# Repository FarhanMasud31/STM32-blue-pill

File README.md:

learning kicad

STM32 blue pill

followed theses as reference:

https://github.com/Jzuni97/STM32-Blue-Pill/tree/main

https://www.youtube.com/watch?v=aVUqaB0IMh4&t=274s

schematic

front copper layer

back copper layer

3D layout

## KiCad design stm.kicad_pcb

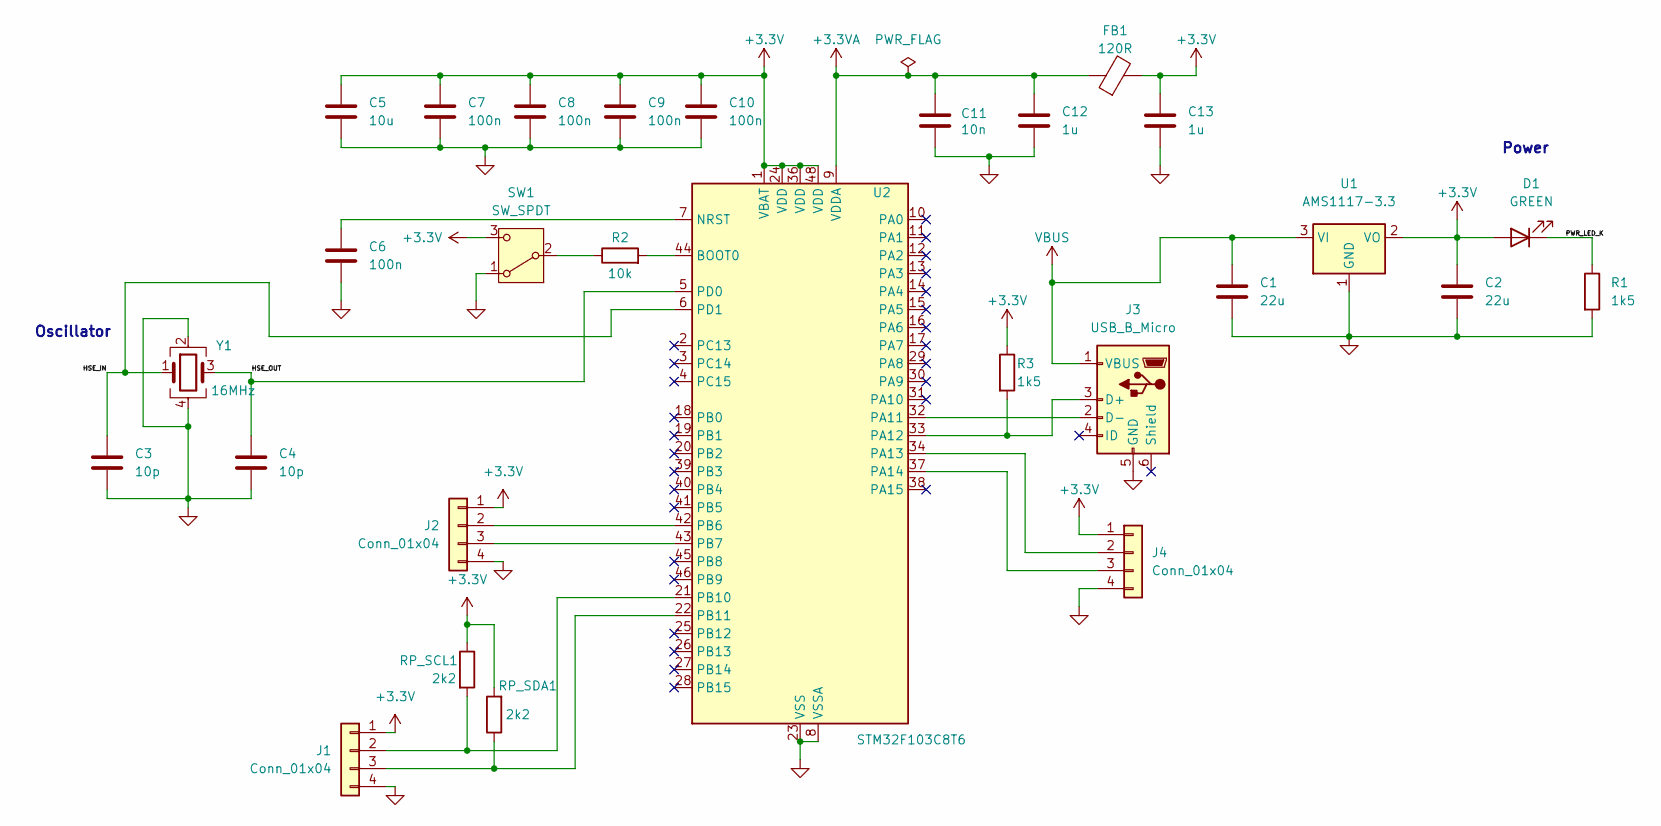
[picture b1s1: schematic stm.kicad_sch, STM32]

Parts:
C1, C2: 22u; C_0805_2012Metric
C3, C4: 10p; C_0402_1005Metric
C5: 10u; C_0603_1608Metric
C6, C7, C8, C9, C10: 100n; C_0402_1005Metric
C11: 10n; C_0402_1005Metric
C12, C13: 1u; C_0402_1005Metric
D1: GREEN; LED_0603_1608Metric
FB1: 120R; L_0603_1608Metric
J1, J2, J4: Conn_01x04; PinHeader_1x04_P2.00mm_Vertical
J3: USB_B_Micro; USB_Micro-B_Wuerth_629105150521
R1, R3: 1k5; R_0402_1005Metric
R2: 10k; R_0402_1005Metric
RP_SCL1: 2k2; R_0402_1005Metric
RP_SDA1: 2k2; R_0402_1005Metric
SW1: SW_SPDT; SW_SPDT_PCM12
U1: AMS1117-3.3; SOT-223-3_TabPin2
U2: STM32F103C8T6; LQFP-48_7x7mm_P0.5mm
Y1: 16MHz; Crystal_SMD_3225-4Pin_3.2x2.5mm

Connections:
+3.3V: C2.1, C5.1, C7.1, C8.1, C9.1, C10.1, C13.1, D1.2 (A), FB1.2, J1.1, J2.1, J4.1, R3.1, RP_SCL1.1, RP_SDA1.2, SW1.3 (C), U1.2 (VO), U2.1 (VBAT), U2.24 (VDD), U2.36 (VDD), U2.48 (VDD)
+3.3VA: C11.1, C12.1, FB1.1, U2.9 (VDDA)
/HSE_IN: C3.1, U2.6 (PD1), Y1.1
/HSE_OUT: C4.1, U2.5 (PD0), Y1.3
/I2C2_SCL: J1.2, RP_SCL1.2, U2.21 (PB10)
/I2C2_SDA: J1.3, RP_SDA1.1, U2.22 (PB11)
/PWR_LED_K: D1.1 (K), R1.1
/USART1_RX: J2.3, U2.43 (PB7)
/USART1_TX: J2.2, U2.42 (PB6)
GND: C1.2, C2.2, C3.2, C4.2, C5.2, C6.2, C7.2, C8.2, C9.2, C10.2, C11.2, C12.2, C13.2, J1.4, J2.4, J3.5 (GND), J4.4, R1.2, SW1.1 (A), U1.1 (GND), U2.8 (VSSA), U2.23 (VSS), U2.35 (VSS), U2.47 (VSS), Y1.2, Y1.4
unnamed: J3.3 (D+), R3.2, U2.33 (PA12)
unnamed: J3.2 (D-), U2.32 (PA11)
unnamed: J4.2, U2.34 (PA13)
unnamed: J4.3, U2.37 (PA14)
unnamed: R2.1, SW1.2 (B)
unnamed: R2.2, U2.44 (BOOT0)
unnamed: C6.1, U2.7 (NRST)
VBUS: C1.1, J3.1 (VBUS), U1.3 (VI)

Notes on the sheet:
Power
Oscillator

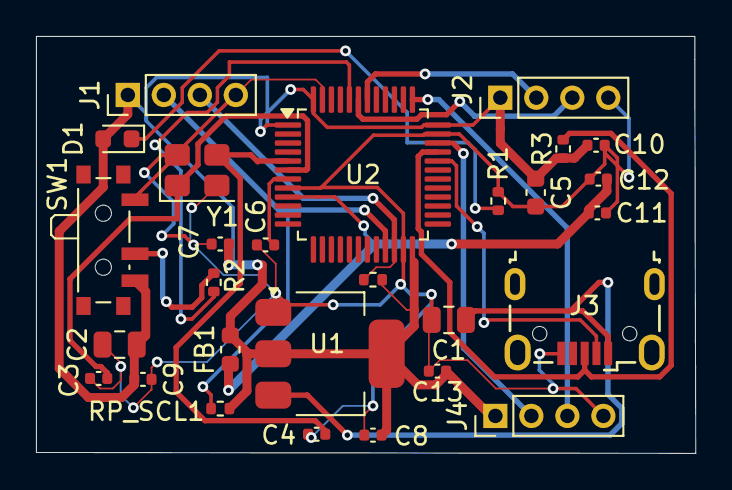
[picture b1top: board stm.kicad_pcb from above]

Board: 2 copper layers, 36.6 x 23.2 mm, 28 parts (0 on the bottom side), 18 nets.
